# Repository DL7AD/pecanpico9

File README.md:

# Pecan Pico 9 - A lightweight APRS tracker for balloons
This Project contains the Pecan Pico project in it's 9th version. A Pecan is a cheap lightweight APRS position tracker designed especially for small ballons which may fly for monthes. This tracker has been made in respect of weight, functionality and price because it's usually used once like a satellite. While the balloon can fly for a long time, this tracker is solar powered and recharges it's battery at daytime and uses the power stored in the battery at night.

Note: The most recent Pecan design is [Pecan Pico 10](http://github.com/DL7AD/pecanpico10/)

<br>
*Pecan Pico 9a*

Other than usual position tracker, this tracker has also the ability to take pictures with a camera and send them to the ground.
The tracker can use RTTY/SSDV to transmit those to the ground. While RTTY can only be received directly, this tracker can also use APRS/SSDV. Therefore SSDV has been integraded into the APRS protocol. This new protocol allows the user to receive pcitures by using their APRS receiver and a computer. There is no tuning required, so everything could work autonomously. APRS has been integrated for the image transmission in respect to be used on the global APRS network itself. So images can be received from far away using the Igating service. Image packets may be received somewhere else by Igates and relayed through the internet. The APRS image transmission could be also used to make use of 9k6 APRS. 9k6 APRS transmits the images very fast. VGA sized pictures can be transmitted within minute. While the protocol doesn't change, using this technique doesn't need any changes rather than the decoding equipment.

<br>
*APRS/SSDV Transmission diagramm*

The camera can sample pictures up to UXGA (1600x1200px) but transmitting those still might take some time. The standard camera OV2640 can be bought for roughly US$5 but it can be replaced by a wide angular camera if needed using the FFC connector. Please don't expect high quality images. VGA sized pictures (640x480px) are okay but you might see the bad quality if you ramp up the resolution. Note that this tracker cannot save the pictures. That might be possible in theory but the chip (STM32F413) does only contain 1MB Flash memory and that might be enough for 20 pictures only. Here are some images which have been taken and transmitted by APRS/SSDV.

<br>
*Closed Airport Berlin Tempelhof roughly 3km (10,000ft) altitude*

<br>
*Test picture from the ground*

<br>
*Lakes in East Poland (Myślibórz) at 8km (25,000ft) altitude, antenna and radar reflector in the picture*

<br>
*South East Berlin (Adlershof/Grünau) taken at roughly 5km (16,000ft) altitude*

The tracker can transmit pictures, GPS data and telemetry data simultanously. That means that the picture transmission can be interrupted and GPS data can be sent in between. While all data can be transmitted by APRS, there is only one decive being needed to receive all the data. APRS itself doesn't need any tuning (like RTTY) so receivers may be left unattended to operate automatically. Using APRS-IS (Igates) additionally reduces the risk of missing packets. If one station miss one packet, it could be received by a different station. All packets are put together and decoded on a central server.

### GNSS
The Pecan provides a ublox EVA-7M GPS chip for localizing the tracker. It can operate up to 50km. This is important because regular GNSS receivers operate only up to 18km (60,000ft) usually and balloons may fly higher. The EVA-7M can only receive GPS. The footprint on the PCB is compabile to the ublox EVA-M8M. This GNSS chip can also receive GLONASS and and the new European GNSS network Galileo too. I have chosen the predecessor while it consumes less power. The EVA-7M can be acessed by the STM32 by UART or I2C. However the software does use UART. If there would be an error on the I2C bus, the GNSS chip will still continue to work. To avoid any interferences, the EVA-7M isn't connected to the I2C bus. It can be connected by assembling 0R resistors.

The GPS is powered through a dedicated low noise LDO with 3.3V. This LDO can be switched on and off by the STM32. The antenna can be connected by an IPEX connector on the bottom. There can be also soldered an antenna directly on the top of the PCB which have to be 4.5cm long.

<br>
*GNSS Antenna*

### Power management
The Pecan can be powered by LiPO batteries but also by primary lithium batteries.

If you want to use the tracker on a Latex balloon, you may use lithium batteries by Energizer which can withstand very cold temperatures (don't use Varta!). These type of batteries come in two sizes: AA and AAA. Using AAA batteries should provide sufficient power for a continous transmission of 12 hours. The battery connector of the Pecan is connected to a buck converter which can handle up to 6V. 3 batteries should be put into series and connected to it. The tracker should work flawlessly until the battery reaches 3V and should still continue to work until a input voltage of ~2V is reached. While a AAA battery weights 11.5g, the tracker has a high weight of ~45g. Primary batteries may be preferred because it's very simple to assemble.

<br>
*Pecan Pico 8a assembled with primary batteries*

if you want to use a foil balloon which may fly at least for some days, you would rather stick to LiPO batteries. LiPO batteries are used with solar cells in common which can be soldered to the backside of the Pecan or connected to pinheaders on the side. The Pecan can be also used with solar cells only but it wouldn't work at night.

At night temperatures low as -50°C can be reached. So operating the tracker with LiPO batteries is quite difficult but not impossible. If the operation can be reduced to transmission only, the tracker might work trough the night. Aquiring a GPS fix may draw too much current. At the moment, there is no good solution for this problem yet, so you might stop the GPS operation at night.
The LiPO battery should be connected to the battery terminals on the backside of the Pecan. If a solar cell is connected to the Pecan too, it will charge the battery. The battery can also be charged trough USB. Solar cells must not be connected with USB at the same time while USB while both supplies are connected on the same network. The USB voltage is fed through 2 silicon diodes to the SPV1040. This has been done because USB may provide up to 5.5V, which is too much for the SPV1040's input.

The solar and battery voltage can be measured by voltage dividers connected to the STM32. In respect to save energy, those dividers have an impedance of 32kOhm. While the STM32 has a low input impedance too, the measurement is probably not that accurate. Therefore the PAC1720 can be used which can measure voltage and current consumption at the same time. This chip can be accessed by I2C and is fairly accurate.

The following picture shows a power management diagram of the Pecan Pico 9a

<br>
*Power Diagram*

The internal operation voltage of the microcontroller and transmitter is 1.8V. This voltage has been chosen while the microcontroller draws less power at low voltages. However USB operatopm requires 3V at least. Also the transmitter does radiate less power at low voltages. Therefore the operation voltage can be ramped up either by connecting a USB host or by the *V_BOOST* pin of the STM32.

A USB host (like a computer) does provide a GND signal through the USB ID pin. This pin was originally used to indicate a USB host has been connected (rather than a slave). On the Pecan this pin is connected to the feedback resistor network of the buck converter. If USB is connected the voltage is ramped up to 3.0V. It isn't possible to connect USB slaves (like a USB stick) to the Pecan, because USB slaves don't provide a GND signal on the USB ID pin. So the STM32 will run at 1.8V which is insufficient voltage for USB operation.

### Transmitter
The transmitter is based on a Si4063 which can do up to 100mW (at an operation voltage of 3.3V). It is able to transmit FSK, GFSK and OOK (On/Off-Keying). 2FSK is better known as RTTY and OOK as CW (morse). 2GFSK can be used for 9k6 APRS. APRS 1k2 which uses AFSK is archived by a 2GFSK modulation. The chip itself has never been intended to modulate AFSK, but its possible. The Pecan has a 2m low pass filter (LPF), so it cannot transmit on the 70cm band. Transmitting at 70cm would be possible by the chip, if the LPF is replaced by a 70cm version. Due to the low operation voltage (1.8V), the Pecan does transmit only at 30...40mW in general. This should be enough for APRS operation. However it is possible to ramp up the operation voltage to 3.0V by the microcontroller itself and get up to 70...80mW.

###

Unsolved problems
=================

As mentioned before, the battery might freeze at night. LiPO's are already a good option and I don't know a battery which works better. LiPO's work best at warm temperatures (~20°C). At low temperatures the battery has a high internal resistance, which reduces the possible amount of current that can be used until the battery voltage drops too much. So what can we do? There are three options:

- Make the battery larger => Problem: It increases the total weight
- Heat the battery => Problem: It might need a larger battery to heat it all trough the night and that increases the total weight
- Draw less current

Option one and two are bad. Having more weight means that we can only fly at lower altitudes. The possibility to get into rain at a low altitude is much higher. Recovering the balloon from rain is impossible. It will descent to the gound, caught by a tree and it will never fly again.

So the only option is, to draw less current. Idling and a short APRS transmission is okay for the battery. Measuring the temperature, airpressure and humidity is okay too. However aquiring a GPS fix draws too much current.

Author
======

Please let me know if you have questions or ideas: sven.steudte@gmail.com

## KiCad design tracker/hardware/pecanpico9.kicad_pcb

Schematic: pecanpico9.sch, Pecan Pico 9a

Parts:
C1, C31: 22u; C_0805
C2: 1n; C_0402
C3, C4, C6: 10u; C_0805
C5, C24, C26: 22p; C_0402
C8, C9, C10, C11, C12, C13, C22, C37, C39, C40, C51: 2u2; C_0402
C14, C20, C23, C29, C30, C33, C35, C43, C44, C45, C46, C48: 100n; C_0402
C15, C16, C34: 100p; C_0402
C18, C19: 470p; C_0402
C25, C27: 3.3p; C_0402
C28: 1u; C_0402
C32, C38: 10n; C_0402
D2: blue; LED_0603
D3: green; LED_0603
D7: red; LED_0603
D8, D9: RFN1L7STE25; RFN1L7S; Mouser 755-RFN1L7STE25
IC1: SPV1040T; TSSOP-8_4.4x3mm_Pitch0.65mm; Mouser 511-SPV1040T
IC2: TPS62260DRVR; DFN-6-1EP_2x2mm_Pitch0.65mm; Mouser 595-TPS62260DRVR
IC3: ADP322ACPZ-115-R7; QFN-16-1EP_3x3mm_Pitch0.5mm; Mouser 584-ADP322ACPZ-115R7
IC4: Si4063-B1B-FM; QFN-20-1EP_4x4mm_Pitch0.5mm; Mouser 634-SI4063-B1B-FM
IC5: STM32F413xG; LQFP-64_10x10mm_Pitch0.5mm
IC6: EVA-7M; EVA7M
IC7: PAC1720-1-AIA-TR; DFN-10-1EP_3x3mm_Pitch0.5mm; Mouser 579-PAC1720-1-AIA-TR
IC8: LDLN015PU33R; DFN-6-1EP_2x2mm_Pitch0.5mm; Mouser 511-LDLN015PU33R
IC9: BME280; Mouser 262-BME280
L1: XAL4040-103; XAL4040; Mouser 994-XAL4040-103MEC
L2: LPS3015-222; LPS3015; Mouser 994-LPS3015-222MRC
L3: 470n; C_0805; Mouser 994-0805LS-471XJLB
L4, L6: 56n; C_0805; Mouser 994-0805CS-560XJLC
L5: 82n; C_0805; Mouser 994-0805CS-820XJLC
P1: CONN_01X25; FFC1x24_0.5mm
P2: CONN_01X10; Pin_Header_Straight_1x10
P3: ZX62-B-5PA(33); USB_Micro-B_SMD; Mouser 798-ZX62-B-5PA33
P4, P6: IPX 2mm; IPX_2mm; Mouser 960-RECE20279001E01
P5: CONN_01X02; Pin_Header_Straight_1x02_SMD
Q1: FDN306P; SOT-23; Mouser 512-FDN306P
R1: 220k; R_0402
R2, R9, R14, R17, R23, R24, R28, R31: 100k; R_0402
R3, R5, R33: 22k; R_0402
R4, R6, R32: 10k; R_0402
R7: 510k; R_0402
R8, R36: 249k; R_0402
R10, R11, R21, R35: 1k5; R_0402
R18, R22: 0R1; R_0603; Mouser 667-ERJ-3RSFR10V
R19, R20: N/A; R_0402
R25, R26: 4k7; R_0402
R27: 0R; R_0402
R29, R30: 1k; R_0402
W1, W2, W3, W9: Testpad; PAD_3x1.5
W4, W5: Testpad
W6, W8, W10: Pad; PAD_6x3
W7, W11: Pad; PAD_3x3
X1: KT2016K26000BCW18ZAS; tcxo; Mouser 581-KT2016K2BCW18ZAS

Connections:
+1V8: C5.1, C6.1, C13.1, C14.1, C15.1, C18.1, C23.1, C35.2, C37.1, C38.1, C39.2, C40.2, C43.2, C44.2, C45.2, C46.2, IC4.6 (VBATA), IC4.8 (VBATD), IC5.1 (VBAT), IC5.13 (VDDA/VREF+), IC5.19 (VDD), IC5.32 (VDD), IC5.48 (VDD), IC5.64 (VDD), IC6.21 (VCC_BCKP), IC9.2 (CSB), IC9.5 (SDO), IC9.6 (VDDIO), IC9.8 (VDD), L2.2, L3.2, P5.2, R7.1, R17.2, R23.1, R25.1, R26.1, R27.1, R35.1
+1V35: C12.1, C30.2, IC3.8 (VOUT3), P1.14, P1.15
+3V3: C10.1, D2.2 (A), D3.2 (A), IC3.5 (VOUT1), IC7.10 (VDD)
+BATT: IC7.4 (SENSE2-), P2.1, R22.1, R29.2
+SOL: C1.1, D8.1, IC1.1 (VINSNS), IC1.8 (XSHUNT), IC7.1 (SENSE1+), L1.2, P2.3, R3.1, R18.1, R28.1, W7.1
/ADC_VBAT: IC5.11 (PC3), R5.2, R6.1
/ADC_VSOL: IC5.27 (PB1), R3.2, R4.1
/ADC_VUSB: IC5.24 (PC4), R32.1, R33.2
/BATT_CONN: P2.2, W11.1
/BOOT0: IC5.60 (BOOT0), P5.1, R31.1
/CAM_D2: IC5.14 (PA0), P1.6
/CAM_D3: IC5.15 (PA1), P1.4
/CAM_D4: IC5.16 (PA2), P1.3
/CAM_D5: IC5.17 (PA3), P1.5
/CAM_D6: IC5.20 (PA4), P1.7
/CAM_D7: IC5.21 (PA5), P1.9
/CAM_D8: IC5.22 (PA6), P1.11
/CAM_D9: IC5.23 (PA7), P1.13
/CAM_EN: IC3.15 (EN3), IC3.16 (EN2), IC5.37 (PC6), R14.1
/CAM_HREF: IC5.10 (PC2), P1.16
/CAM_PCLK: IC5.8 (PC0), P1.8
/CAM_RESET: IC5.25 (PC5), P1.19
/CAM_VSYNC: IC5.9 (PC1), P1.18
/CAM_XCLK: IC5.41 (PA8), P1.12
/CLOCK_26M: C16.1, C32.1, X1.3 (FREQ)
/GPS_EN: IC5.52 (PC11), IC8.3 (EN), R9.1
/GPS_RESET: IC5.2 (PC13), IC6.14 (RESET)
/GPS_RXD: IC5.61 (PB8), IC6.16 (TX_MISO), W4.1
/GPS_TXD: IC5.62 (PB9), IC6.15 (RX_MOSI), W5.1
/I2C_SCL: IC5.58 (PB6), IC7.9 (SMCLK), IC9.4 (SCK), P1.20, R19.1, R25.2
/I2C_SDA: IC5.59 (PB7), IC7.8 (SMDATA), IC9.3 (SDI), P1.22, R20.1, R26.2
/IO_LED2: IC5.33 (PB12), R10.2
/IO_LED3: IC5.40 (PC9), R11.2
/IO_TXD: IC5.29 (PB10), P2.5
/RADIO_CS: IC4.15 (CS), IC5.54 (PD2)
/RADIO_GPIO1: IC4.10 (GPIO1), IC5.53 (PC12)
/RADIO_SDN: IC4.1 (SDN), IC5.50 (PA15), R17.1
/SENSE_SOL-: IC7.2 (SENSE1-), Q1.3, R18.2
/SOL_SHORT_EN: IC5.38 (PC7), Q1.1, R28.2
/SPI_MISO: IC4.13 (SDO), IC5.56 (PB4)
/SPI_MOSI: IC4.14 (SDI), IC5.57 (PB5)
/SPI_SCK: IC4.12 (SCK), IC5.55 (PB3)
/SWD_NRST: IC5.7 (NRST), P2.7
/SWD_SWCLK: IC5.49 (PA14), P2.10
/SWD_SWDIO: IC5.46 (PA13), P2.8
/USB_D+: IC5.45 (PA12), P3.3 (D+), R35.2
/USB_D-: IC5.44 (PA11), P3.2 (D-)
/USB_VUSB: D9.2, IC5.42 (PA9), P3.1 (VCC), R33.1
/VCC_GPS: C20.1, C22.1, D7.2 (A), IC6.19 (VCC), IC6.20 (VCC_IO), IC8.6 (OUT)
/V_BOOST: IC5.39 (PC8), P3.4 (ID), R36.2
GND: C1.2, C2.2, C3.2, C4.1, C6.2, C8.2, C9.2, C10.2, C11.2, C12.2, C13.2, C14.2, C15.2, C18.2, C20.2, C22.2, C23.2, C24.2, C26.2, C29.2, C30.1, C31.1, C33.1, C34.1, C35.1, C37.2, C38.2, C39.1, C40.1, C43.1, C44.1, C45.1, C46.1, C48.2, C51.1, IC1.2 (GND), IC2.2 (MODE), IC2.6 (GND), IC2.7 (THERM), IC3.12 (GND), IC3.17 (GND), IC4.18 (GND), IC4.21 (THERMAL), IC5.12 (VSSA/VREF-), IC5.18 (VSS), IC5.31 (VSS), IC5.43 (PA10), IC5.47 (VSS), IC5.63 (VSS), IC6.2 (RF_GND), IC6.7 (V_USB), IC6.9 (RTC_I), IC6.18 (GND), IC6.37 (EP), IC7.5 (GND), IC7.6 (ADDR_SEL), IC7.11 (EP), IC8.4 (GND), IC8.7 (THERM), IC9.1 (GND), IC9.7 (GND), P1.10, P1.17, P1.23, P1.25, P2.4, P2.6, P2.9, P3.5 (GND), P3.6 (shield), P4.2, P6.2, Q1.2, R2.2, R4.2, R6.2, R8.2, R9.2, R14.2, R24.2, R31.2, R32.2, W2.1, W3.1, W10.1, X1.2 (GND)
unnamed: C2.1, IC1.5 (VCTRL), R1.2, R2.1
unnamed: C5.2, IC2.3 (FB), R7.2, R8.1, R36.1
unnamed: C16.2, IC4.17 (XIN)
unnamed: C19.1, L4.2
unnamed: C19.2, IC4.4 (TX), L3.1
unnamed: C24.1, C25.1, L4.1, L5.2
unnamed: C25.2, C26.1, C27.1, L5.1, L6.2
unnamed: C27.2, L6.1, P4.1, W1.1
unnamed: C28.1, IC1.6 (ICTRL-), R29.1
unnamed: C28.2, IC1.7 (ICTRL+), R30.1
unnamed: C32.2, IC5.5 (PH0-OSC_IN)
unnamed: C51.2, IC5.30 (VCAP_1)
unnamed: D2.1 (K), R10.1
unnamed: D3.1 (K), R11.1
unnamed: D7.1 (K), R21.1
unnamed: D8.2, D9.1
unnamed: IC1.3 (LX), L1.1
unnamed: IC2.1 (SW), L2.1
unnamed: IC6.1 (RF_IN), P6.1, W9.1
unnamed: IC6.29 (SCL_SCK), R19.2
unnamed: IC6.30 (SDA_CS), R20.2
unnamed: IC6.31 (TIMEPULSE), R21.2
unnamed: R23.2, R24.1, X1.1 (AFC)
unnamed: W6.1, W8.1
VDD: C3.1, C4.2, C8.1, C9.1, C29.1, IC1.4 (VOUT), IC2.4 (EN), IC2.5 (VIN), IC3.1 (EN1), IC3.2 (VBIAS), IC3.3 (VIN1/VIN2), IC3.10 (VIN3), IC7.3 (SENSE2+), IC8.1 (IN), R1.1, R5.1, R22.2, R30.2
VDDA: C11.1, C31.2, C33.2, C34.2, IC3.6 (VOUT2), P1.21

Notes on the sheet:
USB only work with USB hosts like computer. The USB ID pin used to switch VCC from 1.8V to 3.3V USB Slaves like USB Sticks do not work, because USB ID pin is not connected to STM32.
Voltage can be measured by IC7
Duplicate BME280 on the camera daughter board. IC9 may be used instead of IC8 because it is more far away from heat sources. It may measure the temperature and humidity more accurately. Note: IC8 and IC9 have different addresses.
V_BOOST is pulled down by STM32 or by USB Host. When V_BOOST is pulled down the TPS62260 will switch to 3.0V. This is necessary for USB commu- nication and to get more power out of the Si4464. V_BOOST must not be pulled high because the TPS62260 will fail.
ADP controls the supply voltage for the camera and the GPS. Both need a clean voltage.
Put jumper on Pins 10 and 11 in order to connect the battery to the actual circuit. So you don't have to desolder the battery everytime.
Battery
Solar
Debug
Programming
Battery connection pads
Solar left-to-right interconnection
Solar cells must be connected to pad W7 and W10.
The battery can be charged by USB. The USB supply is not connected directly to the SPV1040 while the input voltage must not exceed by 4.1V.
Camera connector and Atmosphere sensor
2m Transceiver
Power
GPS
Connectors
+BATT Directly connected to battery +SOL Solar network VDD Connected to battery through sense resistor +1V8 Main power supply for STM32 and transmitter +3V3 LED and PAC1720 power supply +VDDA Analog power supply for camera +1V35 Core power supply for camery (actually 1.8V)
If SOL_SHORT_EN is enabled, the current of the solar cell can be measured by the PAC1720
BOOT1!

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
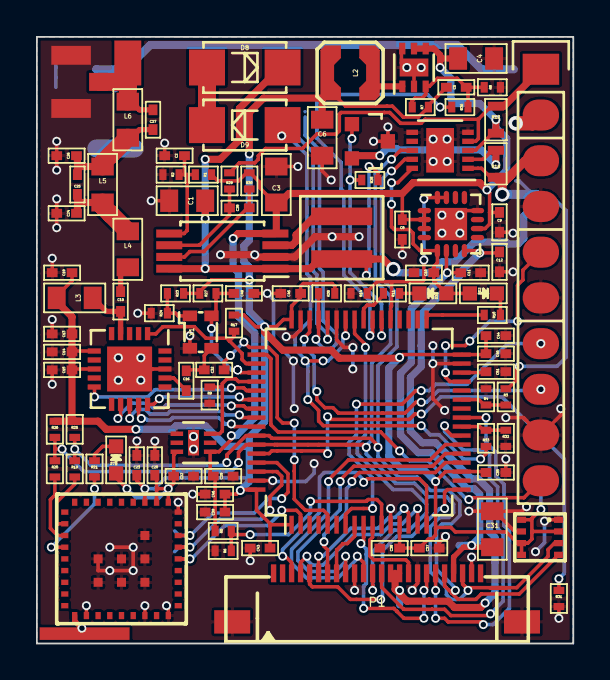
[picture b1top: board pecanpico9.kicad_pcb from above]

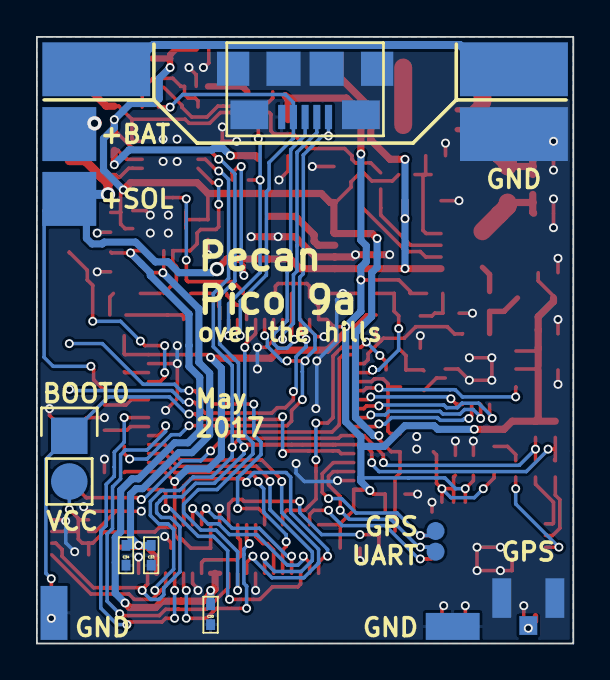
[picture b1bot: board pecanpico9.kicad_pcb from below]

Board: 2 copper layers, 29.8 x 33.7 mm, 112 parts (15 on the bottom side), 78 nets.

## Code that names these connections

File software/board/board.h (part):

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 */

// IO
#define IO_TXD                      (GPIOB, 10U)
// #define IO_RXD                      (GPIOB, 11U) // used for CAM_EN on Pecan Pico 8a
#define IO_LED1                     (GPIOB, 1U)
#define IO_LED2                     (GPIOB, 0U)
#define IO_LED3                     (GPIOE, 8U)
#define IO_LED4                     (GPIOE, 14U)

// GPS
#define GPS_EN                      (GPIOF, 3U)
#define GPS_TIMEPULSE               (GPIOB, 4U)
#define GPS_RESET                   (GPIOD, 7U)
#define GPS_IRQ                     (GPIOC, 10U)
#define GPS_TXD                     (GPIOC, 12U)
#define GPS_RXD                     (GPIOD, 2U)

// I2C
#define I2C_SCL                     (GPIOB, 8U)
#define I2C_SDA                     (GPIOB, 9U)

// SPI
#define SPI_SCK                     (GPIOB, 13U)
#define SPI_MISO                    (GPIOB, 14U)
#define SPI_MOSI                    (GPIOB, 15U)

// Camera pins
#define CAM_XCLK                    (GPIOA, 8U)
#define CAM_PCLK                    (GPIOA, 6U)
#define CAM_HREF                    (GPIOA, 4U)
#define CAM_VSYNC                   (GPIOB, 7U)
#define CAM_D2                      (GPIOC, 6U)
#define CAM_D3                      (GPIOC, 7U)
#define CAM_D4                      (GPIOC, 8U)
#define CAM_D5                      (GPIOC, 9U)
#define CAM_D6                      (GPIOE, 4U)
#define CAM_D7                      (GPIOB, 6U)
#define CAM_D8                      (GPIOE, 5U)
#define CAM_D9                      (GPIOE, 6U)
#define CAM_EN                      (GPIOB, 11U)
#define CAM_RESET                   (GPIOA, 3U)

// Radio pins
#define RADIO_CS                    (GPIOD, 9U)
#define RADIO_SDN                   (GPIOD, 12U)
#define RADIO_GPIO0                 (GPIOD, 10U)
#define RADIO_GPIO1                 (GPIOD, 8U)
#define RADIO_IRQ                   (GPIOD, 11U)

// ADC
#define ADC_VSOL                    (GPIOA, 3U)
#define ADC_VBAT                    (GPIOC, 5U)
#define ADC_VUSB                    (GPIOA, 7U)

// PAC1720
#define PAC_ALERT                   (GPIOB, 12U)
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#define OSC_P1                      (GPIOD, 13U)
#define OSC_P2                      (GPIOD, 14U)
#define OSC_P3                      (GPIOD, 15U)
#define SOL_SHORT_EN                (GPIOE, 10U)
#define CLOCK_26M                   (GPIOH, 0U)



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/*
 * GPIOA setup:
 *
 * PA0  - UART_TX                   (alternate 8)
 * PA1  - UART_RX                   (alternate 8)
 * PA2  - UART_GPS_TX               (alternate 7)
 * PA3  - UART_GPS_RX               (alternate 7)
 * PA4  - CAM_HREF                  (alternate 13)
 * PA5  - PIN5                      (input pullup)
 * PA6  - CAM_PCLK                  (alternate 13)
 * PA7  - RADIO_PWR_REF            (input floating)
 * PA8  - CAM_XCLK                  (alternate 0)
 * PA9  - RADIO_GPIO1              (output pushpull maximum)
 * PA10 - RADIO_GPIO0              (output pushpull maximum)
 * PA11 - RADIO_CS                 (output pushpull maximum)
 * PA12 - RADIO_SDN                (output pushpull maximum)
 * PA13 - SWDIO                     (alternate 0)
 * PA14 - SWCLK                     (alternate 0)
 * PA15 - SD_CS                     (output pushpull maximum)
 */
#define VAL_GPIOA_MODER             (PIN_MODE_INPUT(GPIOA_PIN0) |    \
                                     PIN_MODE_INPUT(GPIOA_PIN1) |    \
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 * GPIOB setup:
 *
 * PB0  - RADIO2_CS                 (output pushpull maximum)
 * PB1  - RADIO_PWR_SENSE          (input floating)
 * PB2  - BOOT1                     (input pullup)
 * PB3  - SWO                       (alternate 0)
 * PB4  - PIN4                      (input pullup)
 * PB5  - PIN5                      (input pullup)
 * PB6  - CAM_D7                    (alternate 13)
 * PB7  - CAM_VSYNC                 (alternate 13)
 * PB8  - CAM_SCL                   (alternate 4)
 * PB9  - CAM_SDA                   (alternate 4)
 * PB1  - I2C_SCL                   (alternate 4)
 * PB11 - I2C_SDA                   (alternate 4)
 * PB12 - RADIO2_SDN                (output pushpull maximum)
 * PB13 - SPI_SCK                   (alternate 5)
 * PB14 - SPI_MISO                  (alternate 5)
 * PB15 - SPI_MOSI                  (alternate 5)
 */
#define VAL_GPIOB_MODER             (PIN_MODE_INPUT(GPIOB_IO_LED2) |     \
                                     PIN_MODE_INPUT(GPIOB_IO_LED1)|\
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/*
 * GPIOC setup:
 *
 * PC0  - PIN0                      (input pullup)
 * PC1  - PIN1                      (input pullup)
 * PC2  - PIN2                      (input pullup)
 * PC3  - PIN3                      (input pullup)
 * PC4  - ADC_VSOLAR                (input pullup)
 * PC5  - ADC_VBAT_DIFF             (input floating)
 * PC6  - CAM_D2                    (alternate 13)
 * PC7  - CAM_D3                    (alternate 13)
 * PC8  - CAM_D4                    (alternate 13)
 * PC9  - CAM_D5                    (alternate 13)
 * PC10 - SD_SCK                    (alternate 6)
 * PC11 - SD_MISO                   (alternate 6)
 * PC12 - SD_MOSI                   (alternate 6)
 * PC13 - LED_2YELLOW                (output pushpull maximum)
 * PC14 - OSC32_IN                  (input floating)
 * PC15 - LED_1RED                   (output pushpull maximum)
 */
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 *
 * PD0  - PIN0                      (input pullup)
 * PD1  - PIN1                      (input pullup)
 * PD2  - PIN2                      (input pullup)
 * PD3  - PIN3                      (input pullup)
 * PD4  - PIN4                      (input pullup)
 * PD5  - PIN5                      (input pullup)
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/*
 * GPIOE setup:
 *
 * PE0  - CAM_EN                   (output pushpull maximum)
 * PE1  - PIN1                      (input pullup)
 * PE2  - PIN2                      (input pullup)
 * PE3  - LED_3GREEN                 (input pullup)
 * PE4  - CAM_D6                    (alternate 13)
 * PE5  - CAM_D8                    (alternate 13)
 * PE6  - CAM_D9                    (alternate 13)
 * PE7  - GPS_EN                    (output pushpull maximum)
 * PE8  - PIN8                      (input pullup)
 * PE9  - PIN9                      (input pullup)
 * PE10 - GPS_TIMEPULSE             (input pullup)
 * PE11 - PIN11                     (input pullup)
 * PE12 - GPS_RESET                 (output pushpull maximum)
 * PE13 - RADIO2_GPIO0              (output pushpull maximum)
 * PE14 - RADIO2_GPIO1              (output pushpull maximum)
 * PE15 - MPU_INT                   (input pullup)
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/*
 * GPIOH setup:
 *
 * PH0  - PIN0                      (input pullup)
 * PH1  - PIN1                      (input pullup)
 * PH2  - PIN2                      (input pullup)
 * PH3  - PIN3                      (input pullup)
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
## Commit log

2017-05-22 Initial upload commit
2017-05-22 Wiggled parts around
2017-05-23 Connected VUSB correctly to PA9
2017-05-23 Moved wire around
2017-05-23 Wiggled traces around, created Gerber
2017-05-26 Added BOM and pos files
2017-05-27 Updated BOM
2017-05-28 Added general readme
2017-05-28 Added picture of Pecan Pico 9a
2017-05-30 Moved tracker related files
2017-05-30 Moved tracker related files 2
2017-05-30 Added decoder software
2017-05-30 Deleted build files
2017-05-30 Removed build files
2017-05-30 Deleted KiCAD cache files
2017-05-30 Updated gitignore
2017-05-31 Updated decoder software Implemented stdin connection Implemented APRS-IS connection Implemented error handling at internet loss
2017-06-12 Brought basic operation to work USB not working yet Only QVGA working Radio is working GPS is not working yet BME1720 and PAC1720 working
2017-06-15 Implemented "Line" driver Renamed ublox driver Removed unused files Fixed STM32 ADC driver (incorrect solar reading) Implemented Solar short current measurement Merged Cofigurationt types Lowered Cor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
2017-06-15 Fixed SOT-23 footprint (wrong numbering) Moved LEDs (so they are not too close to the very big inductor) Added Pulldown to GPS_EN
2017-06-15 Added time to print
2017-06-20 Added documentation in config Merged configuration types Made USB and 3V switch configureable Removed USB debugging temporarly Adjusted camera clocking Removed Si4464 power conversion function Implem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
2017-06-20 added ship and car symbols
2017-06-20 add include aprs.h
2017-06-21 correction APRS SYM_CAR HEX value
2017-06-22 Fixed logging error Made camera sampling faster (reduced SYSCLK)
2017-06-30 Implemented camera buffer overflow protection Moved definitions around Changed Isol (PAC1720) measurement implementation Reimplemented logging and log transmission Changed Sleep implementation
2017-06-30 Added decoder scripts
2017-07-01 Fixed read last log point from memory
2017-07-01 Changed GPS switch decisions
2017-07-01 Implemented active USB detection on startup
2017-07-07 Implemented STM32F413 (instead of STM32F412)
2017-07-24 Implemented hardware camera driver
2017-07-26 Implemented shell, worked on camera driver (not working)
2017-08-18 Implemented OV5640
2017-08-19 Try to fix buffer overflow crash
2017-08-19 Removed locking mechanism for I2C
2017-08-19 Revision of ov5640.c dma interrupt handling.
2017-08-19 Removed ChibiOS
2017-08-19 Fixed variable name
2017-08-19 Removed SOI search
2017-08-20 Fixed DMA release error
2017-08-20 Reduced clocking speed
2017-08-20 Adjusted clock speeds
2017-08-21 Flipped PCLK polarity, added TIM8 patch file
2017-08-21 Added JPEG validation filter, changed method of last packet detection
2017-08-21 Add DMA DBM as multi-buffer handling for OV5640
2017-08-22 Fixed DMA error, implemented image size detection
2017-08-22 Increased I2C speed
2017-08-22 Added DMA transaction size
2017-08-22 Added more debugging
2017-08-23 Add saving of DMA flags so TRACE can output specific errors. Add TRACE messages for DMA error conditions. Consolidate DMA error condition flags. Add clear for DMA transfer full interrupt. Tidy up som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
2017-08-27 Fixed radio kept swiched on When a picture was sent, the radio was kept switched on. The detection of the image EOI did not work for the packet transmission because the EOI detection returned the met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
2017-08-28 Adjusted clocks Flipped image in OV5640 driver Fixed spelling
2017-08-28 Fixed faulty image transmission, implemented server exception handling in decoder
2017-08-28 Removed duplicate GPS printout, added more debugging at PVT Polling
2017-08-30 Adjusted clocks for low power operation (camera fix no implemented yet)
2017-08-30 Finalized clockling (so far) for power savings. All dividers for all clocks are static except for HPRE. HPRE is dynamically changed between /1 and /8. It is usually set to /8. If the camera is captur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
    The clock change has a drastic effect of the power consumption.
    --------------------------------------------------
    Running at 1.8V
    Position packet transmission, APRS AFSK, one pac
2017-08-31 Removed backup files
2017-09-01 Implemented RBAT (Battery impedance measurement) Removed ISOL Added LOWBATT message in APRS position packet
2017-09-01 Removed OV2640, implemented testimage
2017-09-01 Tidy up
2017-09-02 Updated SSDV
2017-09-02 Implemented Si4464 packet handler
2017-09-02 Fixed redundant TX error, fixed keep-tx-state-after-transmission error
2017-09-03 Implemented grouped transmissions
2017-09-03 Implemented group transmission, implemented camera init once
2017-09-05 Reimplemented Packet handler for 2GFSK Changed timer implementation for 2FSK Implemented concurrent transmission and packet encoding (not working yet) Wrote documentation for config.c Implemented gro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
2017-09-05 Added... OR of EVT bits, blocking of init of fifo thread until it finishes.
2017-09-06 add gui decoder
2017-09-06 Implemented grouped APRS packet transmission properly Fixed packet losses (incomplete)
2017-09-06 Changed USB implementation
2017-09-06 Fixed packet losses
2017-09-06 Use SPI3 instead of SPI1, fixed radio/camera mutex bug
2017-09-06 Implemented QQVGA
2017-09-07 Added special STM32F413 ChibiOS version
2017-09-07 Implemented piping over RAM
2017-09-07 Decreased uC speed, lowered mem for image thred, changed 2GFSK to 2FSK modulation
2017-09-07 add ssdv for OSX X
2017-09-07 Added USB switch in config
2017-09-07 Implemented SSDV USB transmission, updated decoder for SSDV over USB receiption
2017-09-07 Reimplemented 2GFSK modulation
2017-09-08 Improved image over USB implementation, created python decoder script
2017-09-08 Removed OSC+ net and salvaging pin for Si4464 Changed a lot of STM32 connections
2017-09-08 Increased FIFO buffer in Si4464 to 129bytes Decreased buffer of USB image capturing Removed defines.h Moved mutex initialization to radio.c and image.c
2017-09-08 Increased image sampling speed
2017-09-10 Writing images to file removed, added image counter
2017-09-10 Fixed bug: Image transmission over USB was only possible when debug on USB was activated Fixed bug: Image transmission over USB was only possible when no image module was activated Added feature: Pri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
2017-09-11 - Merged dbgon and dbgoff command to debug - Fixed error in SOI-not-found flag in debug.c - Added camera-command command (for testing different camera options while watching the livestream) - Fixed t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
2017-09-12 Fixed image id initialization error
2017-09-13 Fixed syntax bug in OV5640 Implemented OV5640 configurations which work for sure without HREF (tested on PP7 with DCMI) Adjusted clocking for camera
2017-09-14 Reactivated DMA DBM
2017-09-15 Added connection of PCLK to PC6 so the PCLK is sampled directly from a timer which is capable of triggering the DMA. Before a LPTIM1/TIM1 cascade was used which lead to errors in the DMA transmission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
2017-09-17 Fixed build error
2017-09-19 Added voltage change when using OV5640 Added I2C Lock around voltage change methods Implemented RBAT sleep methods Fixed I2C init problem, reordered initialization methods
2017-09-19 Removed APRS library and implemented native Telnet connection instead
2017-09-19 Added connection watchdog to decoder script Added callsign decoder to decoder script
2017-09-19 Implemented receiver detection correctly
2017-09-23 Removed I2C 0R resistors, removed USB diodes, Added USB ID
2017-10-02 Implemented Base128 and new packet type for APRS picture transmission
2017-10-02 Reimplemented Base91 Changed message buffer implementation Removed error transmission Moved getFrequency implementation to radio.c
2017-10-07 Modified Base91 characters Modified APRS format of Image and Log packets Implemented image Added memory address to log command (Serial USB console) Added failsafe to ADC measurements (if PAC1720 fail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
2017-10-08 Split image packets in half, fixed timezone bug
2017-10-14 Removed STM32 based modulation and moved task to PH of Si4464 (so stable HSE is not needed for STM32 anymore which was needed for radio modulation) Fixed receiver value in decoder.py Limited data dis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
2017-10-16 Implemented UART/I2C switch for GPS Implemented LOWBATT1 and LOWBATT2 Switch off camera at JPEG validation process Moved JPEG validation section Added GPS communication error message Changed Watchdog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
2017-10-16 Fixed decoder error
2017-10-29 Added exception handler
2017-10-31 Fixed uBlox I2C compile error
2017-12-12 Fixed GPS communication error
2017-12-12 Removed time limit in decoder
2017-12-14 Reverted post hardware changes to produced version There was the plan to create Pecan Pico 9b, but all those changes have been put into Pecan Pico 10a.
2018-01-09 Updated APRS protocols and much more - Removed secondary decoder - Updated image encoding at tracker firmware - Updated image encoding at decoder software - Implemented more sophisticated website - A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
2018-01-11 Implemented Log packets for the last protocol changes
2018-01-13 Fixed camera sampling bug
2018-01-21 Implemented Berlin Geofence
2018-02-06 Changed APRS server
2018-02-06 Fixed SQL error
2018-08-06 Made tracking struct compatible to most recent decoder
2018-08-06 Inverted power measurement

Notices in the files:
software/board/board.h:
ChibiOS - Copyright (C) 2006..2015 Giovanni Di Sirio
Licensed under the Apache License, Version 2.0 (the "License");
